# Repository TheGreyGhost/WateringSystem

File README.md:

# WateringSystem
 Arduino + PICAXE automated garden watering system
 
 Supported by a JetBrains Open Source Suppport development licence 09052022/9341100

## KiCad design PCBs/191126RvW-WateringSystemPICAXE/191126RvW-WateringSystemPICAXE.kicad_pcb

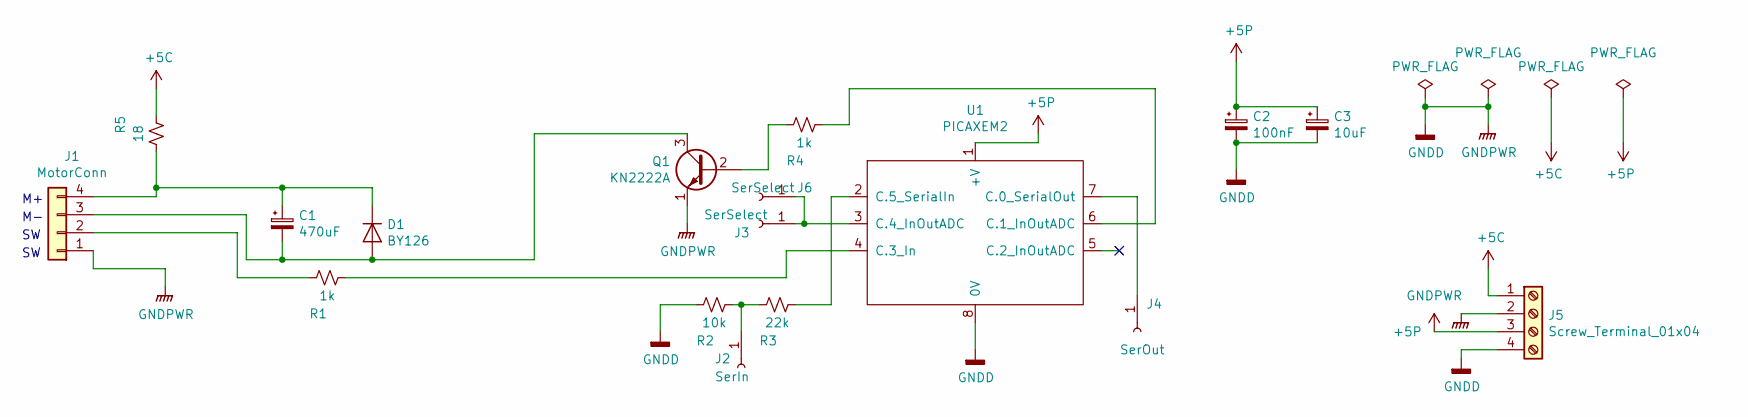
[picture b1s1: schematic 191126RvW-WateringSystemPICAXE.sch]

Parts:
C1: 470uF; CP_Radial_D10.0mm_P5.00mm
C2: 100nF; C_Disc_D4.3mm_W1.9mm_P5.00mm
C3: 10uF; CP_Radial_D5.0mm_P2.50mm
D1: BY126; D_DO-27_P15.24mm_Horizontal
J1: MotorConn; PinHeader_1x04_P2.54mm_Vertical
J2: SerIn; Pin_D1.0mm_L10.0mm
J3, J6: SerSelect; Pin_D1.0mm_L10.0mm
J4: SerOut; Pin_D1.0mm_L10.0mm
J5: Screw_Terminal_01x04; TerminalBlock_Altech_AK300-4_P5.00mm
Q1: KN2222A; TO-92_Inline
R1, R4: 1k; R_Axial_DIN0922_L20.0mm_D9.0mm_P25.40mm_Horizontal
R2: 10k; R_Axial_DIN0922_L20.0mm_D9.0mm_P25.40mm_Horizontal
R3: 22k; R_Axial_DIN0922_L20.0mm_D9.0mm_P25.40mm_Horizontal
R5: 18; R_Axial_DIN0922_L20.0mm_D9.0mm_P25.40mm_Horizontal
U1: PICAXEM2; DIP-8_W10.16mm

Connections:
+5C: J5.1, R5.2
+5P: C2.1, C3.1, J5.3, U1.1 (+V)
GNDD: C2.2, C3.2, J1.1, J5.2, J5.4, Q1.1 (E), R2.2, U1.8 (0V)
unnamed: C1.1, D1.1 (K), J1.4, R5.1
unnamed: C1.2, D1.2 (A), J1.3, Q1.3 (C)
unnamed: J1.2, R1.2
unnamed: J2.1, R2.1, R3.2
unnamed: J3.1, J6.1, U1.3 (C.4_InOutADC)
unnamed: J4.1, U1.7 (C.0_SerialOut)
unnamed: Q1.2 (B), R4.2
unnamed: R1.1, U1.4 (C.3_In)
unnamed: R3.1, U1.2 (C.5_SerialIn)
unnamed: R4.1, U1.6 (C.1_InOutADC)

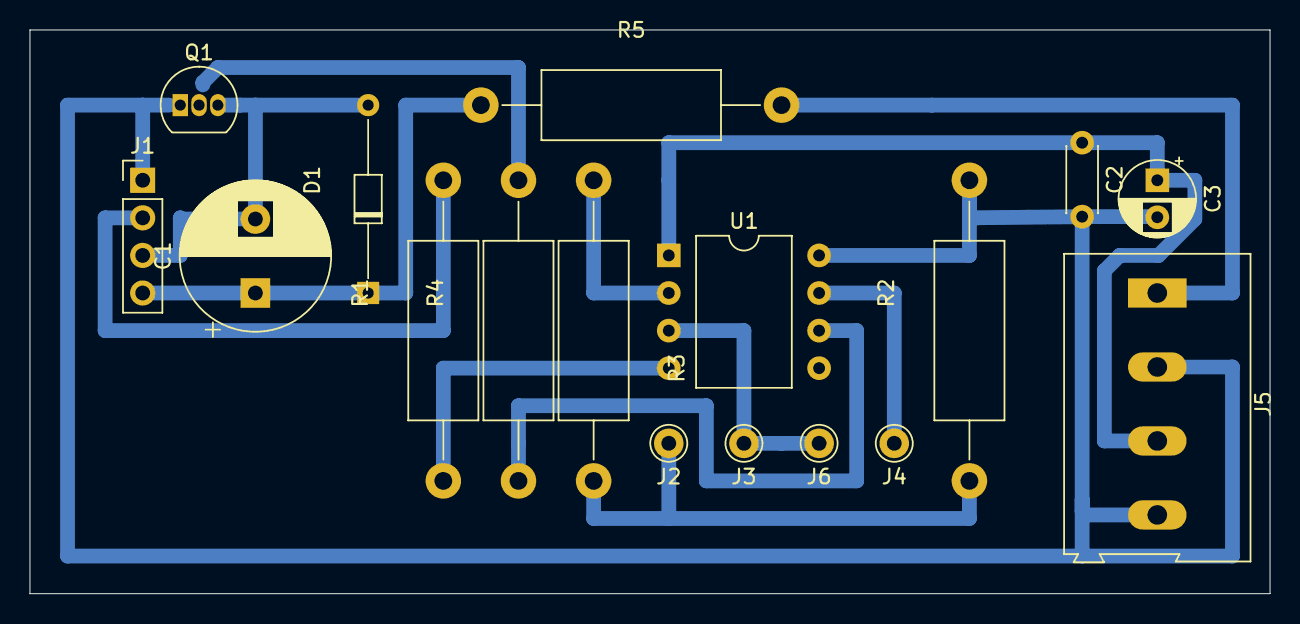
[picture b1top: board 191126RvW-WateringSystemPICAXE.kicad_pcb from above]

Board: 2 copper layers, 83.8 x 38.1 mm, 17 parts (0 on the bottom side), 13 nets.

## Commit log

2019-11-18 Initial Setup
    Initial setup
2019-12-03 Drafting PCBs
2019-12-20 New board size
2020-01-09 Resized board to fit housing
    Small housing
2021-09-13 initial
2021-09-21 picaxe update
2021-09-21 pcb changes
2021-09-21 Test Of Relay Module control
2021-09-24 bugfixes
2021-09-25 working relay module comms
2021-09-25 Starting RS485 tester
2021-09-25 starting testing
2021-09-27 Started transmit code
2021-09-28 picaxe first draft- tested by simulation only
2021-10-16 testing more
2021-10-17 timingcheck
2021-10-17 Works robustly.
    The PICaxe Programmer code works robustly now
2021-10-17 More testing
2021-10-17 PICAXEprogrammer in PICAXE - trying hserin
2021-10-17 Ready for testing
2022-01-17 testing
2022-01-17 tweaking
2022-01-27 mostly working
2022-02-28 Test works correctly
    PICAXE transmits to Arduino correctly.
2022-03-03 Echo test works
2022-03-05 updating to remote control
2022-03-06 Change to pin 3 serin
2022-03-07 Command and response via RS485 is working (with test code still embedded)
2022-03-17 RS485 and relay control commands working (with test code still in place)
2022-03-19 Made PCB
2022-03-20 debug notes added
2022-03-21 bugs fixed
2022-04-21 starting on Arduino control code
2022-04-27 for offline edit without onenote
2022-04-27 bkup
2022-04-28 working on valvesequences
2022-05-05 Working on Sequence
2022-05-10 Application for JetBrains OSS dev licence
2022-07-05 Integrating from CLION test harness, adding remote comms
2022-07-11 fixing syntax errors
2022-07-11 More updates; memory usage reduction
2023-09-30 Not sure what I was up to
